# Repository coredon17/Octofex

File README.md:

# Octofex
FV-1 Eurorack Module

This ia a project that I developed with the help of JLCPCB. The complete details can be found here:

https://jlcpcb.com/fr/?from=ProjectOctofex

The result is the Octofex, a 10HP module with full CV control of the 3 program parameters, plus manual clock speed and blend controls.

The Octofex is largely based on the Traouiero module, designed by Benjamin Bonnal, that is a 20HP stereo module. I opted for a mono module which helped
to reduce the circuit's size, further refinement of the design, splitting out the CV conditioning to separate dual op amps etc. allowed me to fit as much
functionality as possible into the module.

The PCB and panel designs have been verified.

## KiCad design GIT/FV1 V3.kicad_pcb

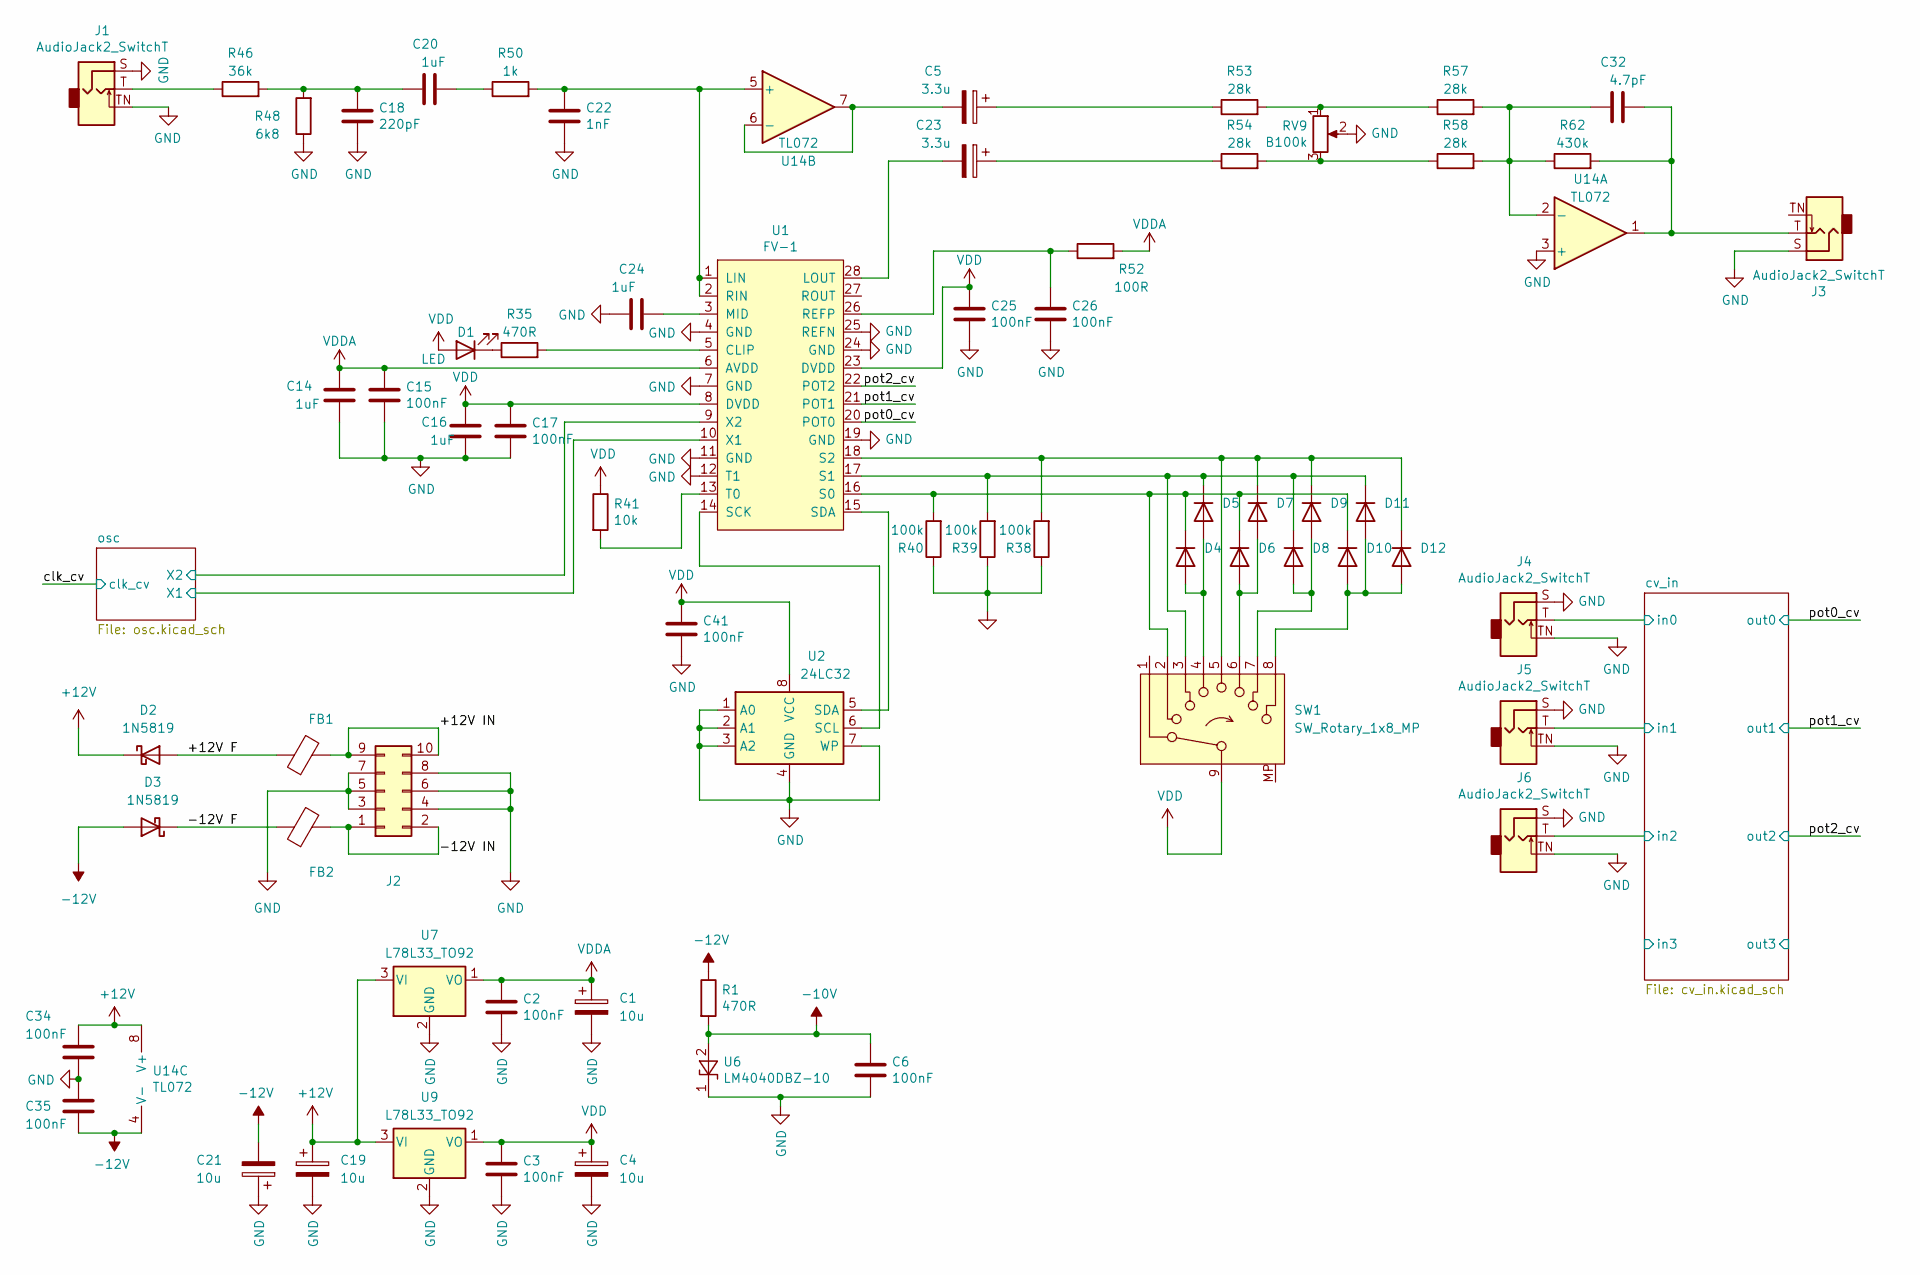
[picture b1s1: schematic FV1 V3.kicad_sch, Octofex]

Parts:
C1, C4, C19, C21: 10u; CP_Radial_D5.0mm_P2.50mm
C2, C3, C6, C15, C17, C25, C26, C34, C35, C41: 100nF; C_0805_2012Metric_Pad1.18x1.45mm_HandSolder
C5, C23: 3.3u; CP_Radial_D5.0mm_P2.50mm
C14, C16, C20: 1uF; C_0805_2012Metric_Pad1.18x1.45mm_HandSolder
C18: 220pF; C_0805_2012Metric_Pad1.18x1.45mm_HandSolder
C22: 1nF; C_0805_2012Metric_Pad1.18x1.45mm_HandSolder
C24: 1uF; CP_EIA-3216-18_Kemet-A_HandSolder
C32: 4.7pF; C_0805_2012Metric_Pad1.18x1.45mm_HandSolder
D1: LED; LED_D3.0mm
D2, D3: 1N5819; D_DO-41_SOD81_P3.81mm_Vertical_AnodeUp
D4, D5, D6, D7, D8, D9, D10, D11, D12: 1N4148W; D_SOD-123
FB1, FB2: FerriteBead; D_DO-41_SOD81_P3.81mm_Vertical_AnodeUp
J1, J3, J4, J5, J6: AudioJack2_SwitchT; Jack_3.5mm_QingPu_WQP-PJ398SM_Vertical_CircularHoles
J2: Conn_02x05_Odd_Even; EuroRack 10W Power
R1, R35: 470R; R_0805_2012Metric_Pad1.20x1.40mm_HandSolder
R38, R39, R40: 100k; R_0805_2012Metric_Pad1.20x1.40mm_HandSolder
R41: 10k; R_0805_2012Metric_Pad1.20x1.40mm_HandSolder
R46: 36k; R_0805_2012Metric_Pad1.20x1.40mm_HandSolder
R48: 6k8; R_0805_2012Metric_Pad1.20x1.40mm_HandSolder
R50: 1k; R_0805_2012Metric_Pad1.20x1.40mm_HandSolder
R52: 100R; R_0805_2012Metric_Pad1.20x1.40mm_HandSolder
R53, R54, R57, R58: 28k; R_0805_2012Metric_Pad1.20x1.40mm_HandSolder
R62: 430k; R_0805_2012Metric_Pad1.20x1.40mm_HandSolder
RV9: B100k; Potentiometer_Alpha_RD901F-40-00D_Single_Vertical
SW1: SW_Rotary_1x8_MP; 8P1T SW
U1: FV-1
U2: 24LC32; DIP-8_W7.62mm
U6: LM4040DBZ-10; SOT-23
U7, U9: L78L33_TO92; TO-92_Inline_Wide
U14: TL072; SOIC-8_3.9x4.9mm_P1.27mm

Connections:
+12V: C19.1, C34.1, D2.1 (K), U7.3 (VI), U9.3 (VI), U14.8 (V+); also elsewhere on the board
-10V: C6.1, R1.2, U6.2 (A); also elsewhere on the board
-12V: C21.2, C35.2, D3.2 (A), R1.1, U14.4 (V-); also elsewhere on the board
/+12V F: D2.2 (A), FB1.1
/+12V IN: FB1.2, J2.9, J2.10
/-12V F: D3.1 (K), FB2.1
/-12V IN: FB2.2, J2.1, J2.2
/cv_in/in0: J4.T; also elsewhere on the board
/cv_in/in1: J5.T; also elsewhere on the board
/cv_in/in2: J6.T; also elsewhere on the board
/osc/X1: U1.10 (X1); also elsewhere on the board
/osc/X2: U1.9 (X2); also elsewhere on the board
/pot0_cv: U1.20 (POT0); also elsewhere on the board
/pot1_cv: U1.21 (POT1); also elsewhere on the board
/pot2_cv: U1.22 (POT2); also elsewhere on the board
GND: C1.2, C2.2, C3.2, C4.2, C6.2, C14.2, C15.2, C16.2, C17.2, C18.2, C19.2, C21.1, C22.2, C24.1, C25.2, C26.2, C34.2, C35.1, C41.2, J1.S, J1.TN, J2.3, J2.4, J2.5, J2.6, J2.7, J2.8, J3.S, J4.S, J4.TN, J5.S, J5.TN, J6.S, J6.TN, R38.1, R39.1, R40.1, R48.1, RV9.2, U1.4 (GND), U1.7 (GND), U1.11 (GND), U1.12 (T1), U1.19 (GND), U1.24 (GND), U1.25 (REFN), U2.1 (A0), U2.2 (A1), U2.3 (A2), U2.4 (GND), U2.7 (WP), U6.1 (K), U7.2 (GND), U9.2 (GND), U14.3 (+); also elsewhere on the board
unnamed: C5.1, R53.1
unnamed: C18.1, C20.2, R46.2, R48.2
unnamed: C20.1, R50.1
unnamed: C23.1, R54.1
unnamed: C32.1, J3.T, R62.2, U14.1
unnamed: D1.1 (K), R35.1
unnamed: D4.2 (A), D5.2 (A), SW1.4
unnamed: D6.2 (A), D7.2 (A), SW1.6
unnamed: D8.2 (A), D9.2 (A), SW1.7
unnamed: D10.2 (A), D11.2 (A), D12.2 (A), SW1.8
unnamed: D4.1 (K), D6.1 (K), D10.1 (K), R40.2, SW1.2, U1.16 (S0)
unnamed: D5.1 (K), D8.1 (K), D11.1 (K), R39.2, SW1.3, U1.17 (S1)
unnamed: D7.1 (K), D9.1 (K), D12.1 (K), R38.2, SW1.5, U1.18 (S2)
unnamed: J1.T, R46.1
unnamed: R53.2, R57.1, RV9.1
unnamed: R54.2, R58.1, RV9.3
unnamed: R35.2, U1.5 (CLIP)
unnamed: C22.1, R50.2, U1.1 (LIN), U1.2 (RIN), U14.5 (+)
unnamed: C23.2, U1.28 (LOUT)
unnamed: C24.2, U1.3 (MID)
unnamed: C26.1, R52.1, U1.26 (REFP)
unnamed: U1.14 (SCK), U2.6 (SCL)
unnamed: U1.15 (SDA), U2.5 (SDA)
unnamed: R41.2, U1.13 (T0)
unnamed: C32.2, R57.2, R58.2, R62.1, U14.2 (-)
unnamed: C5.2, U14.6 (-), U14.7
VDD: C3.1, C4.1, C16.1, C17.1, C25.1, C41.1, D1.2 (A), R41.1, SW1.9, U1.8 (DVDD), U1.23 (DVDD), U2.8 (VCC), U9.1 (VO); also elsewhere on the board
VDDA: C1.1, C2.1, C14.1, C15.1, R52.2, U1.6 (AVDD), U7.1 (VO); also elsewhere on the board

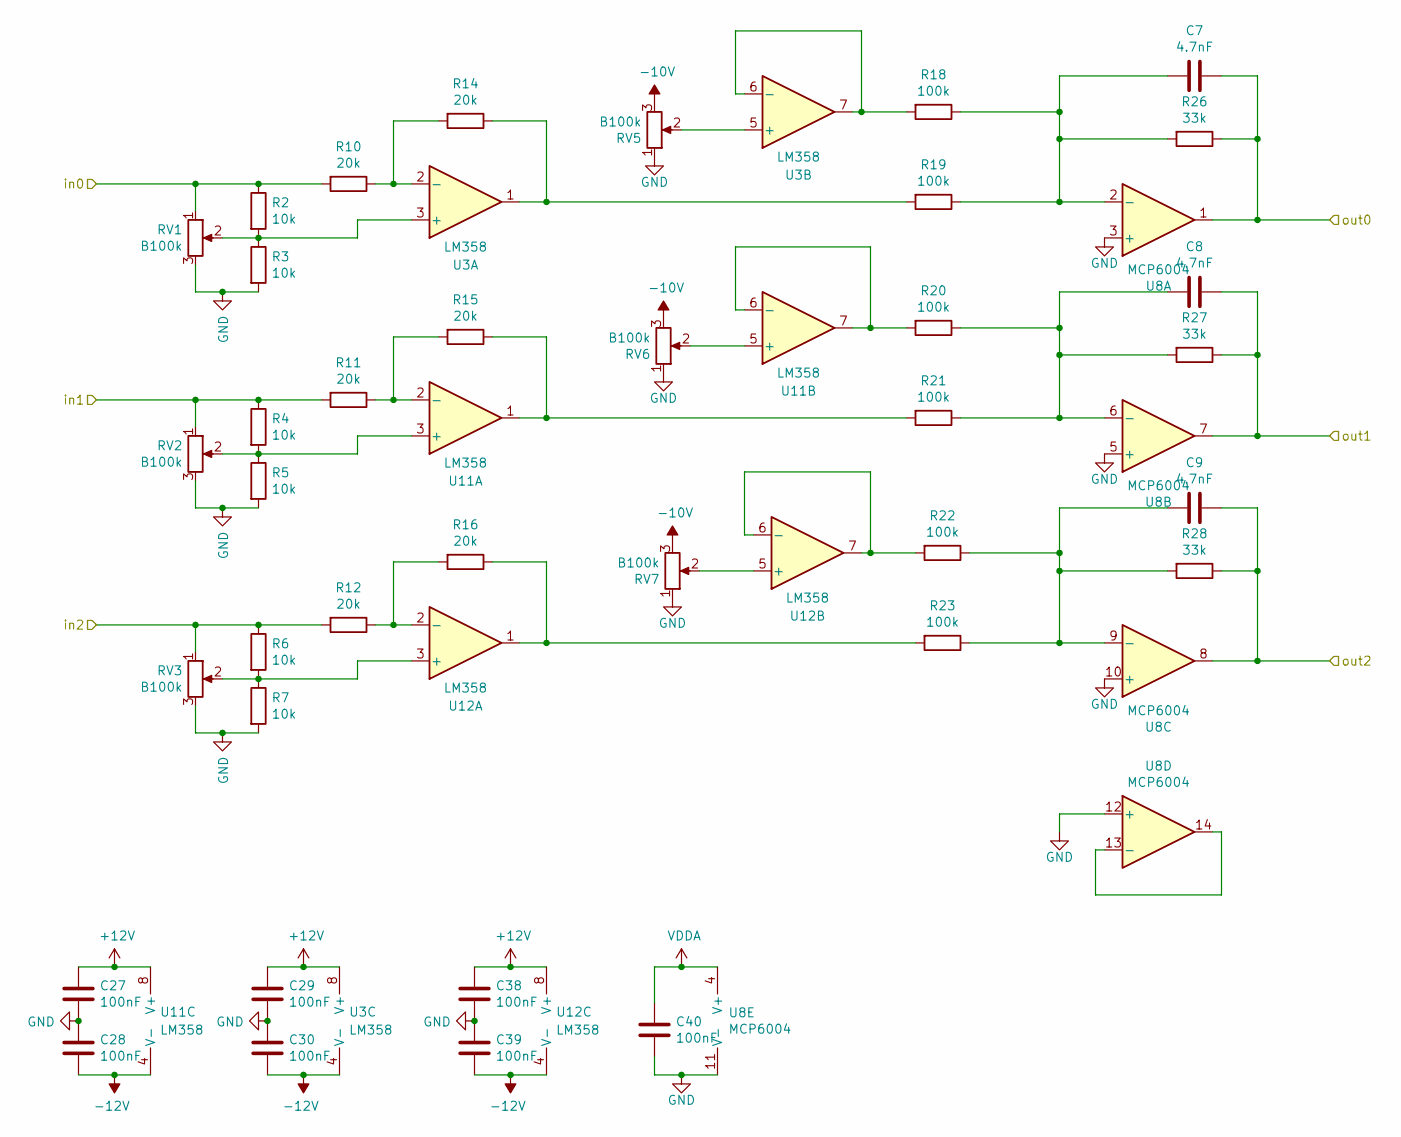
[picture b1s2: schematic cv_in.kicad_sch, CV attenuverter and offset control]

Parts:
C7, C8, C9: 4.7nF; C_0805_2012Metric_Pad1.18x1.45mm_HandSolder
C27, C28, C29, C30, C38, C39, C40: 100nF; C_0805_2012Metric_Pad1.18x1.45mm_HandSolder
R2, R3, R4, R5, R6, R7: 10k; R_0805_2012Metric_Pad1.20x1.40mm_HandSolder
R10, R11, R12, R14, R15, R16: 20k; R_0805_2012Metric_Pad1.20x1.40mm_HandSolder
R18, R19, R20, R21, R22, R23: 100k; R_0805_2012Metric_Pad1.20x1.40mm_HandSolder
R26, R27, R28: 33k; R_0805_2012Metric_Pad1.20x1.40mm_HandSolder
RV1, RV2, RV3: B100k; Potentiometer_Alpha_RD901F-40-00D_Single_Vertical OVAL
RV5, RV6, RV7: B100k; Potentiometer_Alpha_RD901F-40-00D_Single_Vertical
U3, U11, U12: LM358; SOIC-8_3.9x4.9mm_P1.27mm
U8: MCP6004; SOIC-14_3.9x8.7mm_P1.27mm

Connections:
+12V: C27.1, C29.1, C38.1, U3.8 (V+), U11.8 (V+), U12.8 (V+); also elsewhere on the board
-10V: RV5.3, RV6.3, RV7.3; also elsewhere on the board
-12V: C28.2, C30.2, C39.2, U3.4 (V-), U11.4 (V-), U12.4 (V-); also elsewhere on the board
/cv_in/in0: R2.1, R10.2, RV1.1; also elsewhere on the board
/cv_in/in1: R4.1, R11.2, RV2.1; also elsewhere on the board
/cv_in/in2: R6.1, R12.2, RV3.1; also elsewhere on the board
/pot0_cv: C7.1, R26.1, U8.1; also elsewhere on the board
/pot1_cv: C8.1, R27.1, U8.7; also elsewhere on the board
/pot2_cv: C9.1, R28.1, U8.8; also elsewhere on the board
GND: C27.2, C28.1, C29.2, C30.1, C38.2, C39.1, C40.2, R3.2, R5.2, R7.2, RV1.3, RV2.3, RV3.3, RV5.1, RV6.1, RV7.1, U8.3 (+), U8.5 (+), U8.10 (+), U8.11 (V-), U8.12 (+); also elsewhere on the board
unnamed: R14.1, R19.2, U3.1
unnamed: R15.1, R21.2, U11.1
unnamed: R16.1, R23.2, U12.1
unnamed: R2.2, R3.1, RV1.2, U3.3 (+)
unnamed: R10.1, R14.2, U3.2 (-)
unnamed: RV5.2, U3.5 (+)
unnamed: R18.2, U3.6 (-), U3.7
unnamed: C7.2, R18.1, R19.1, R26.2, U8.2 (-)
unnamed: C8.2, R20.1, R21.1, R27.2, U8.6 (-)
unnamed: C9.2, R22.1, R23.1, R28.2, U8.9 (-)
unnamed: U8.13 (-), U8.14
unnamed: R4.2, R5.1, RV2.2, U11.3 (+)
unnamed: R11.1, R15.2, U11.2 (-)
unnamed: RV6.2, U11.5 (+)
unnamed: R20.2, U11.6 (-), U11.7
unnamed: R6.2, R7.1, RV3.2, U12.3 (+)
unnamed: R12.1, R16.2, U12.2 (-)
unnamed: RV7.2, U12.5 (+)
unnamed: R22.2, U12.6 (-), U12.7
VDDA: C40.1, U8.4 (V+); also elsewhere on the board

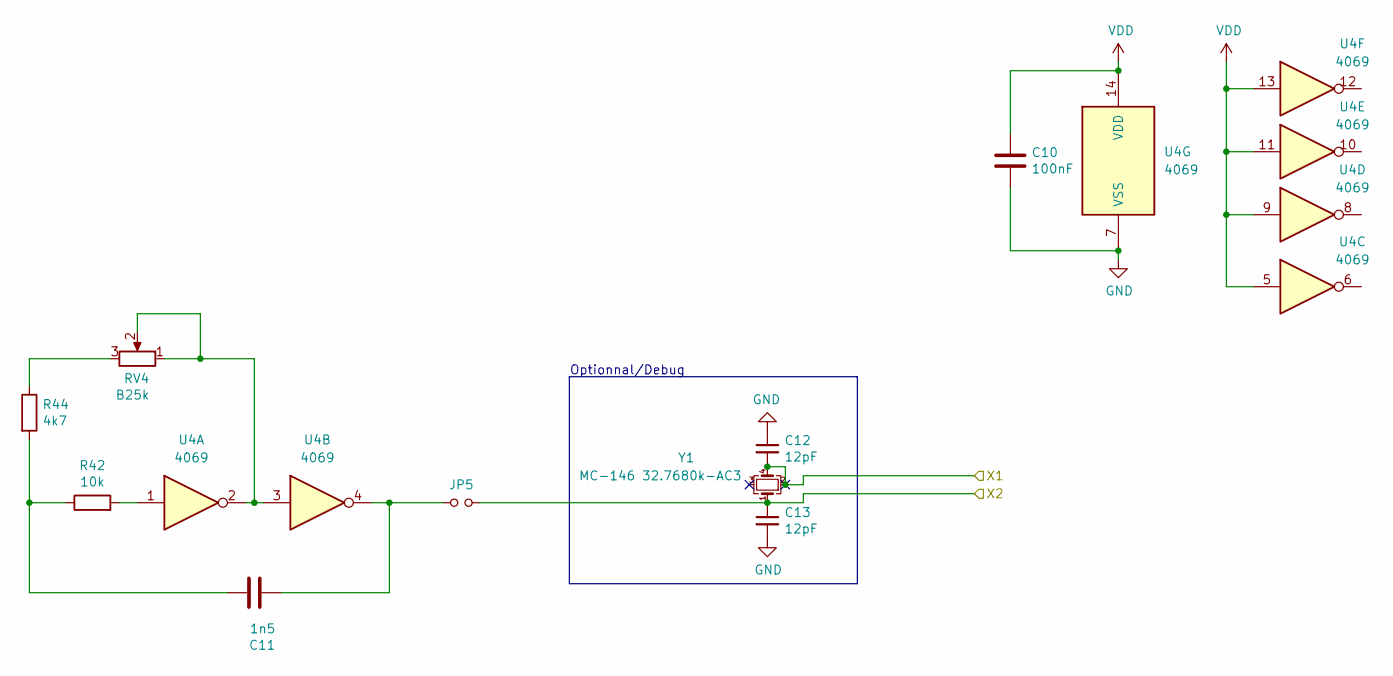
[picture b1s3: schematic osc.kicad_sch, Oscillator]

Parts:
C10: 100nF; C_0805_2012Metric_Pad1.18x1.45mm_HandSolder
C11: 1n5; C_0805_2012Metric_Pad1.18x1.45mm_HandSolder
C12, C13: 12pF; C_0805_2012Metric_Pad1.18x1.45mm_HandSolder
JP5: Jumper_NO_Small; SolderJumper-2_P1.3mm_Open_RoundedPad1.0x1.5mm
R42: 10k; R_0805_2012Metric_Pad1.20x1.40mm_HandSolder
R44: 4k7; R_0805_2012Metric_Pad1.20x1.40mm_HandSolder
RV4: B25k; Potentiometer_Alpha_RD901F-40-00D_Single_Vertical
U4: 4069; SOIC-14_3.9x8.7mm_P1.27mm
Y1: MC-146 32.7680k-AC3; Crystal_DS10_D1.0mm_L4.3mm_Horizontal

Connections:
/osc/X1: C12.2, Y1.2, Y1.4; also elsewhere on the board
/osc/X2: C13.1, JP5.2, Y1.1; also elsewhere on the board
GND: C10.2, C12.1, C13.2, U4.7 (VSS); also elsewhere on the board
unnamed: C11.1, R42.1, R44.2
unnamed: C11.2, JP5.1, U4.4
unnamed: R42.2, U4.1
unnamed: R44.1, RV4.3
unnamed: RV4.1, RV4.2, U4.2, U4.3
VDD: C10.1, U4.5, U4.9, U4.11, U4.13, U4.14 (VDD); also elsewhere on the board

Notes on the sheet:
Optionnal/Debug

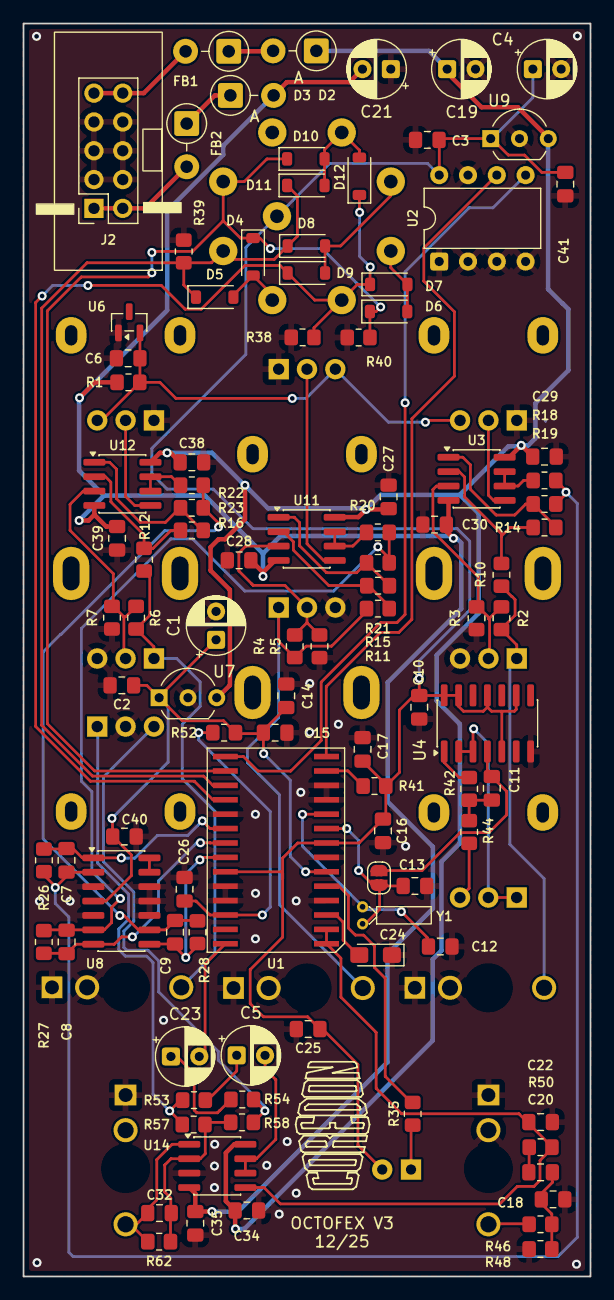
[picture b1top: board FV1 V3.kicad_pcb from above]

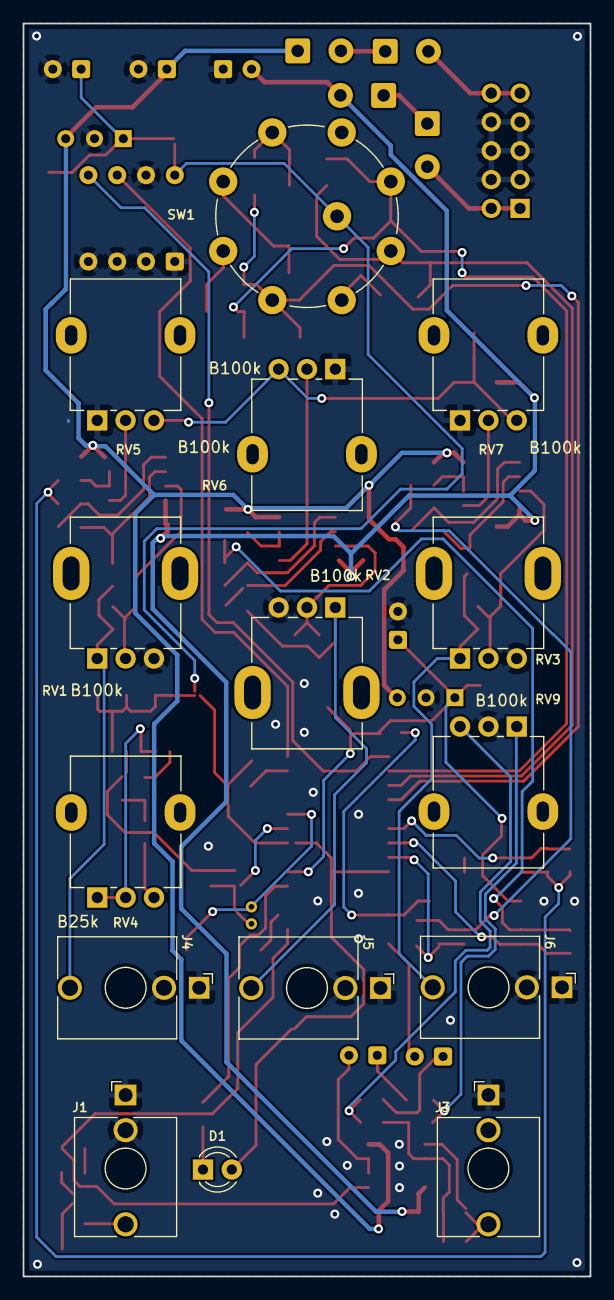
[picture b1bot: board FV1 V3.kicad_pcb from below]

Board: 2 copper layers, 50.0 x 110.5 mm, 117 parts (15 on the bottom side), 68 nets.

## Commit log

2026-02-09 Update README.md
    Edit
2026-02-17 Update README.md
    Add link
2026-02-17 Project Writeups
